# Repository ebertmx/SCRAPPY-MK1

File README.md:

# SCRAPPY-MK1
 A 3D printed robot arm. View documents in project_files for a complete description.
 
 This arm was developed over a 4 week period as an engineering demonstration. Inspired by a previous project, HUEBERT MK2, SCRAPPY consist mostly of 3D printed components and is controllable over the internet (IoT).

The goals of project SCRAPPY were too design and build a robot arm which

1. is highly modular
2. inexpensive
3. had at least 3 DoF
4. could be controlled wireless over a websocket or similar
5. was position and speed controllable
6. used a variety of electrical components (for demonstration purposes)

Other requirements of the specific design can be found in project_files.

The code contained in this respository is designed to run on a 30pin ESP32 Dev module. A python GUI interface is also contained.

This project is ongoing. More details on the use and implementation of this code will be posted when available.

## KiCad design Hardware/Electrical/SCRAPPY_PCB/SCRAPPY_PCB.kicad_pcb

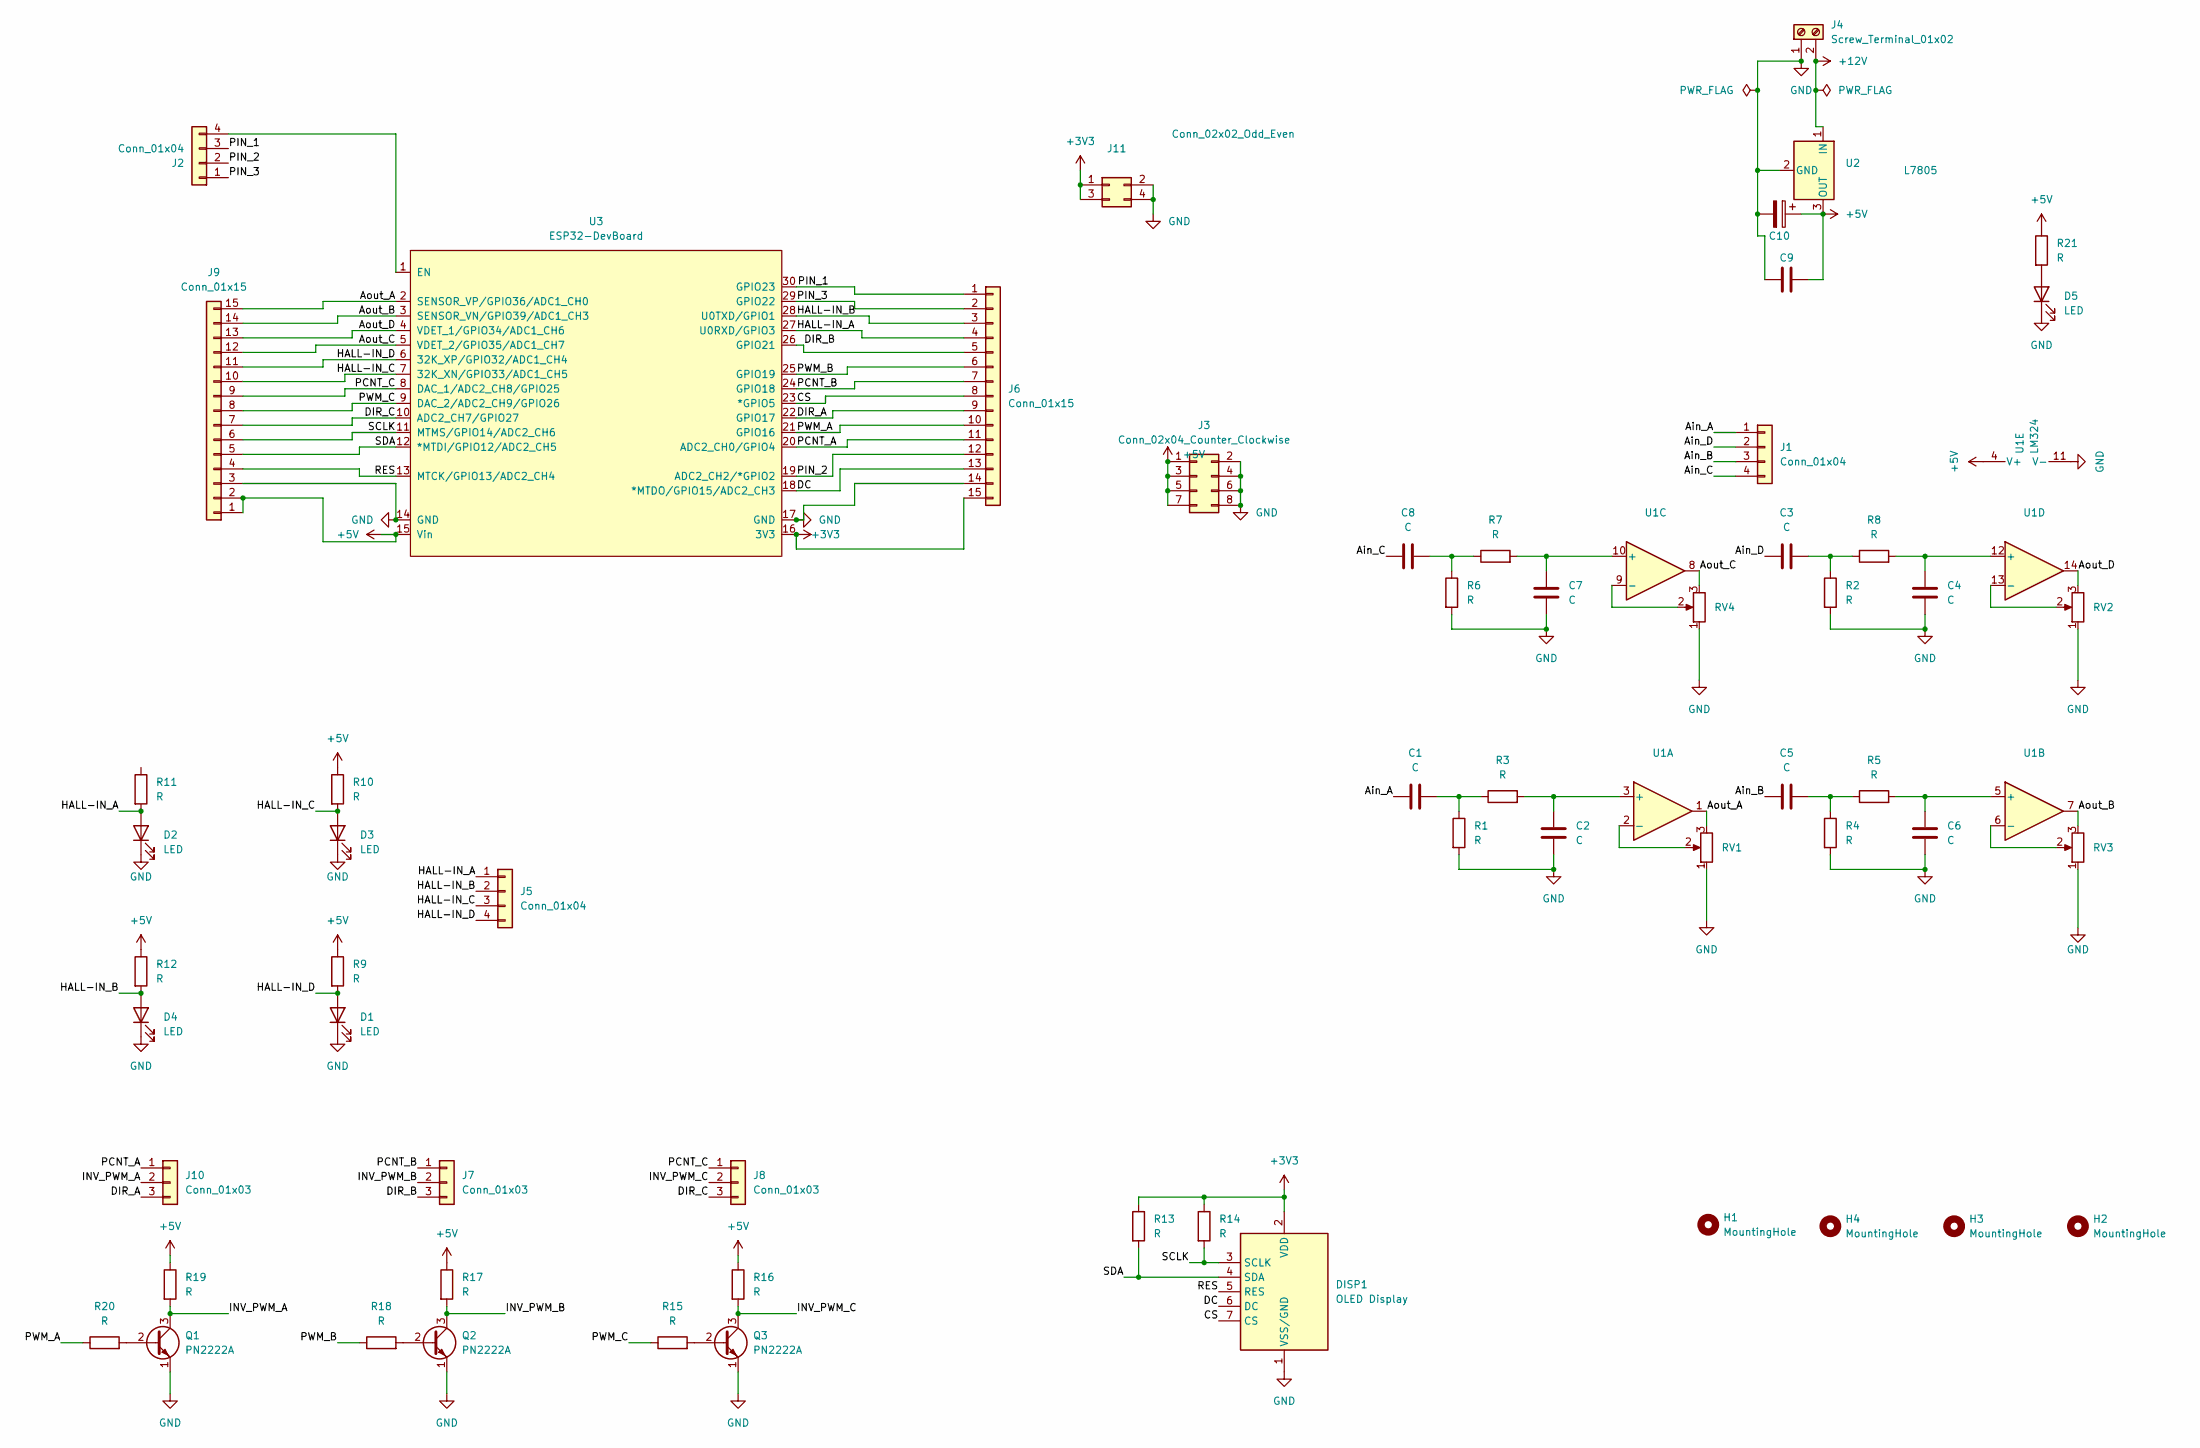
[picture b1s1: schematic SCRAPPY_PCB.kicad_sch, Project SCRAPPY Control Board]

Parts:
C1, C2, C3, C4, C5, C6, C7, C8, C9: C; C_Disc_D3.0mm_W1.6mm_P2.50mm
C10: C_Polarized; CP_Radial_D6.3mm_P2.50mm
D1, D2, D3, D4, D5: LED; LED_D5.0mm_Clear
DISP1: OLED Display; PinHeader_1x07_P2.54mm_Horizontal
H1, H2, H3, H4: MountingHole; MountingHole_2.2mm_M2_DIN965_Pad
J1, J2, J5: Conn_01x04; PinHeader_1x04_P2.54mm_Vertical
J3: Conn_02x04_Counter_Clockwise; PinHeader_2x04_P2.54mm_Vertical
J4: Screw_Terminal_01x02; TerminalBlock_Phoenix_MKDS-1,5-2-5.08_1x02_P5.08mm_Horizont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
J6, J9: Conn_01x15; PinSocket_1x15_P2.54mm_Vertical
J7, J8, J10: Conn_01x03; PinHeader_1x03_P2.54mm_Vertical
J11: Conn_02x02_Odd_Even; PinHeader_1x04_P2.54mm_Vertical
Q1, Q2, Q3: PN2222A; TO-92_Inline_Wide
R1, R2, R3, R4, R5, R6, R7, R8, R9, R10, R11, R12, R13, R14, R15, R16, R17, R18, R19, R20, R21: R; R_Axial_DIN0207_L6.3mm_D2.5mm_P10.16mm_Horizontal
RV1, RV2, RV3, RV4: R_Potentiometer; Potentiometer_Bourns_3296W_Vertical
U1: LM324; DIP-14_W7.62mm_Socket_LongPads
U2: L7805; Converter_DCDC_RECOM_R-78B-2.0_THT
U3: ESP32-DevBoard

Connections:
+3V3: DISP1.2 (VDD), J6.15, J11.1, J11.3, R13.1, R14.1, U3.16 (3V3)
+5V: C9.2, C10.1, J3.1, J3.3, J3.5, J3.7, J9.1, J9.2, R9.1, R10.1, R12.1, R16.1, R17.1, R19.1, R21.1, U1.4 (V+), U2.3 (OUT), U3.15 (Vin)
+12V: J4.2, U2.1 (IN)
/Ain_A: C1.1, J1.1
/Ain_B: C5.1, J1.3
/Ain_C: C8.1, J1.4
/Ain_D: C3.1, J1.2
/Aout_A: J9.15, RV1.3, U1.1, U3.2 (SENSOR_VP/GPIO36/ADC1_CH0)
/Aout_B: J9.14, RV3.3, U1.7, U3.3 (SENSOR_VN/GPIO39/ADC1_CH3)
/Aout_C: J9.12, RV4.3, U1.8, U3.5 (VDET_2/GPIO35/ADC1_CH7)
/Aout_D: J9.13, RV2.3, U1.14, U3.4 (VDET_1/GPIO34/ADC1_CH6)
/CS: DISP1.7 (CS), J6.8, U3.23 (*GPIO5)
/DC: DISP1.6 (DC), J6.13, U3.18 (*MTDO/GPIO15/ADC2_CH3)
/DIR_A: J6.9, J10.3, U3.22 (GPIO17)
/DIR_B: J6.5, J7.3, U3.26 (GPIO21)
/DIR_C: J8.3, J9.7, U3.10 (ADC2_CH7/GPIO27)
/HALL-IN_A: D2.2 (A), J5.1, J6.4, R11.2, U3.27 (U0RXD/GPIO3)
/HALL-IN_B: D4.2 (A), J5.2, J6.3, R12.2, U3.28 (U0TXD/GPIO1)
/HALL-IN_C: D3.2 (A), J5.3, J9.10, R10.2, U3.7 (32K_XN/GPIO33/ADC1_CH5)
/HALL-IN_D: D1.2 (A), J5.4, J9.11, R9.2, U3.6 (32K_XP/GPIO32/ADC1_CH4)
/INV_PWM_A: J10.2, Q1.3 (C), R19.2
/INV_PWM_B: J7.2, Q2.3 (C), R17.2
/INV_PWM_C: J8.2, Q3.3 (C), R16.2
/PCNT_A: J6.11, J10.1, U3.20 (ADC2_CH0/GPIO4)
/PCNT_B: J6.7, J7.1, U3.24 (GPIO18)
/PCNT_C: J8.1, J9.9, U3.8 (DAC_1/ADC2_CH8/GPIO25)
/PIN_1: J2.3, J6.1, U3.30 (GPIO23)
/PIN_2: J2.2, J6.12, U3.19 (ADC2_CH2/*GPIO2)
/PIN_3: J2.1, J6.2, U3.29 (GPIO22)
/PWM_A: J6.10, R20.1, U3.21 (GPIO16)
/PWM_B: J6.6, R18.1, U3.25 (GPIO19)
/PWM_C: J9.8, R15.1, U3.9 (DAC_2/ADC2_CH9/GPIO26)
/RES: DISP1.5 (RES), J9.4, U3.13 (MTCK/GPIO13/ADC2_CH4)
/SCLK: DISP1.3 (SCLK), J9.6, R14.2, U3.11 (MTMS/GPIO14/ADC2_CH6)
/SDA: DISP1.4 (SDA), J9.5, R13.2, U3.12 (*MTDI/GPIO12/ADC2_CH5)
GND: C2.1, C4.1, C6.1, C7.1, C9.1, C10.2, D1.1 (K), D2.1 (K), D3.1 (K), D4.1 (K), D5.1 (K), DISP1.1 (VSS/GND), J3.2, J3.4, J3.6, J3.8, J4.1, J6.14, J9.3, J11.2, J11.4, Q1.1 (E), Q2.1 (E), Q3.1 (E), R1.2, R2.2, R4.2, R6.2, RV1.1, RV2.1, RV3.1, RV4.1, U1.11 (V-), U2.2 (GND), U3.14 (GND), U3.17 (GND)
unnamed: C1.2, R1.1, R3.1
unnamed: C2.2, R3.2, U1.3 (+)
unnamed: C3.2, R2.1, R8.1
unnamed: C4.2, R8.2, U1.12 (+)
unnamed: C5.2, R4.1, R5.1
unnamed: C6.2, R5.2, U1.5 (+)
unnamed: C7.2, R7.2, U1.10 (+)
unnamed: C8.2, R6.1, R7.1
unnamed: D5.2 (A), R21.2
unnamed: J2.4, U3.1 (EN)
unnamed: Q1.2 (B), R20.2
unnamed: Q2.2 (B), R18.2
unnamed: Q3.2 (B), R15.2
unnamed: RV1.2, U1.2 (-)
unnamed: RV2.2, U1.13 (-)
unnamed: RV3.2, U1.6 (-)
unnamed: RV4.2, U1.9 (-)

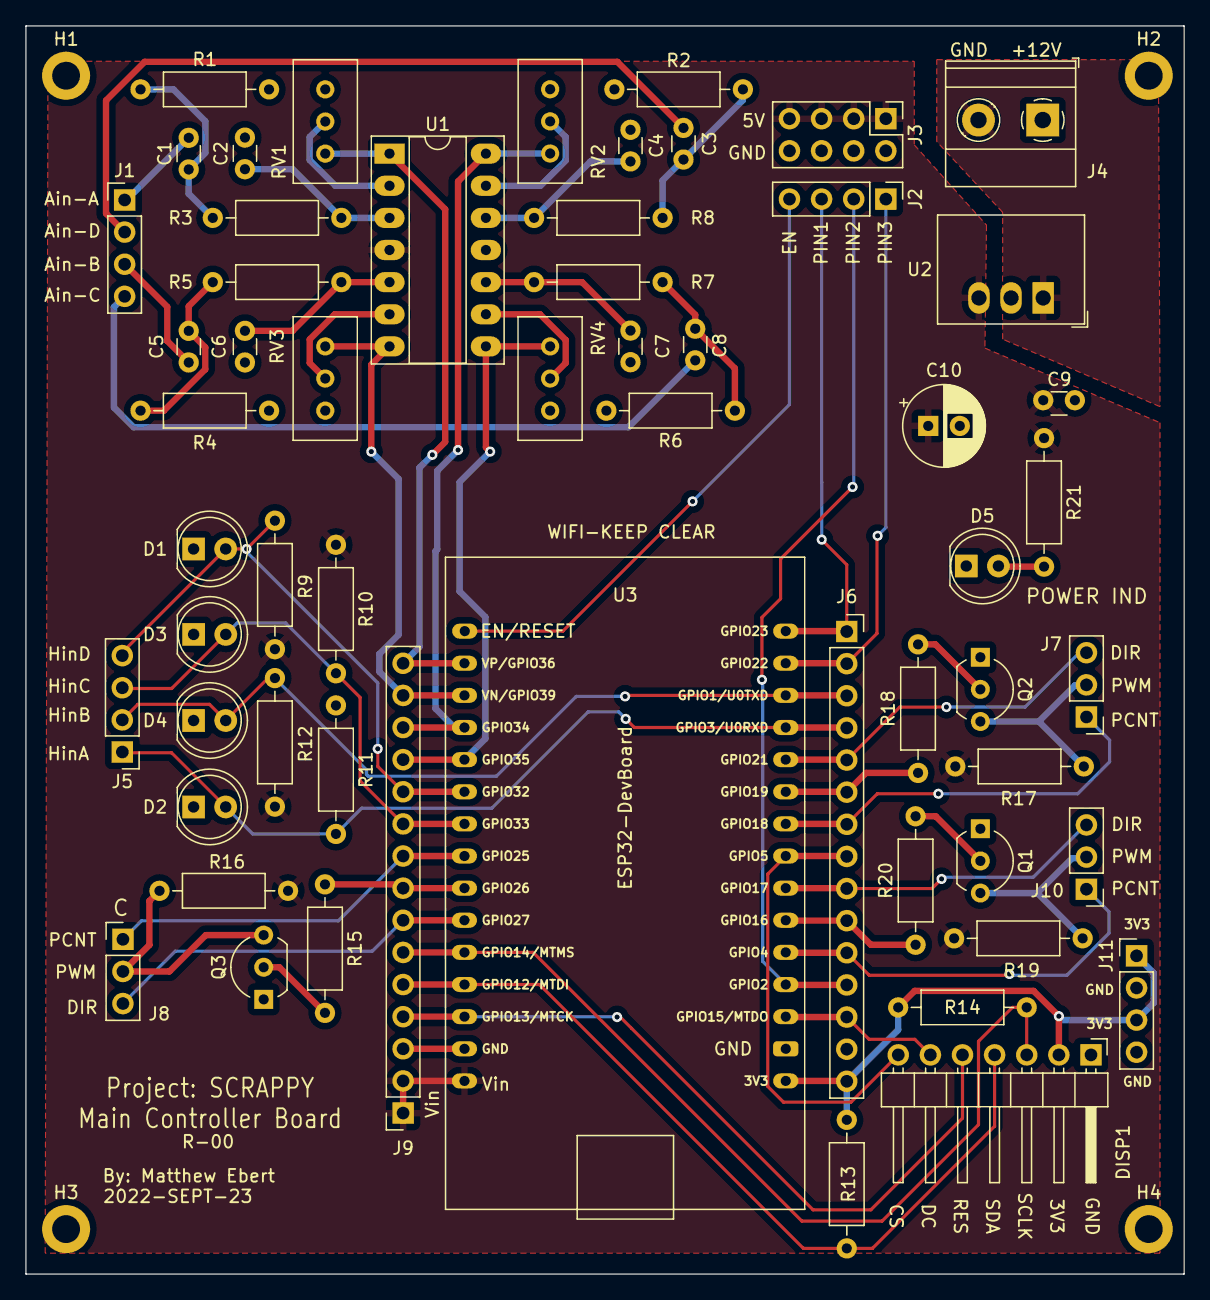
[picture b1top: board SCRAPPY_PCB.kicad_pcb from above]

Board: 2 copper layers, 91.6 x 98.7 mm, 62 parts (0 on the bottom side), 53 nets.

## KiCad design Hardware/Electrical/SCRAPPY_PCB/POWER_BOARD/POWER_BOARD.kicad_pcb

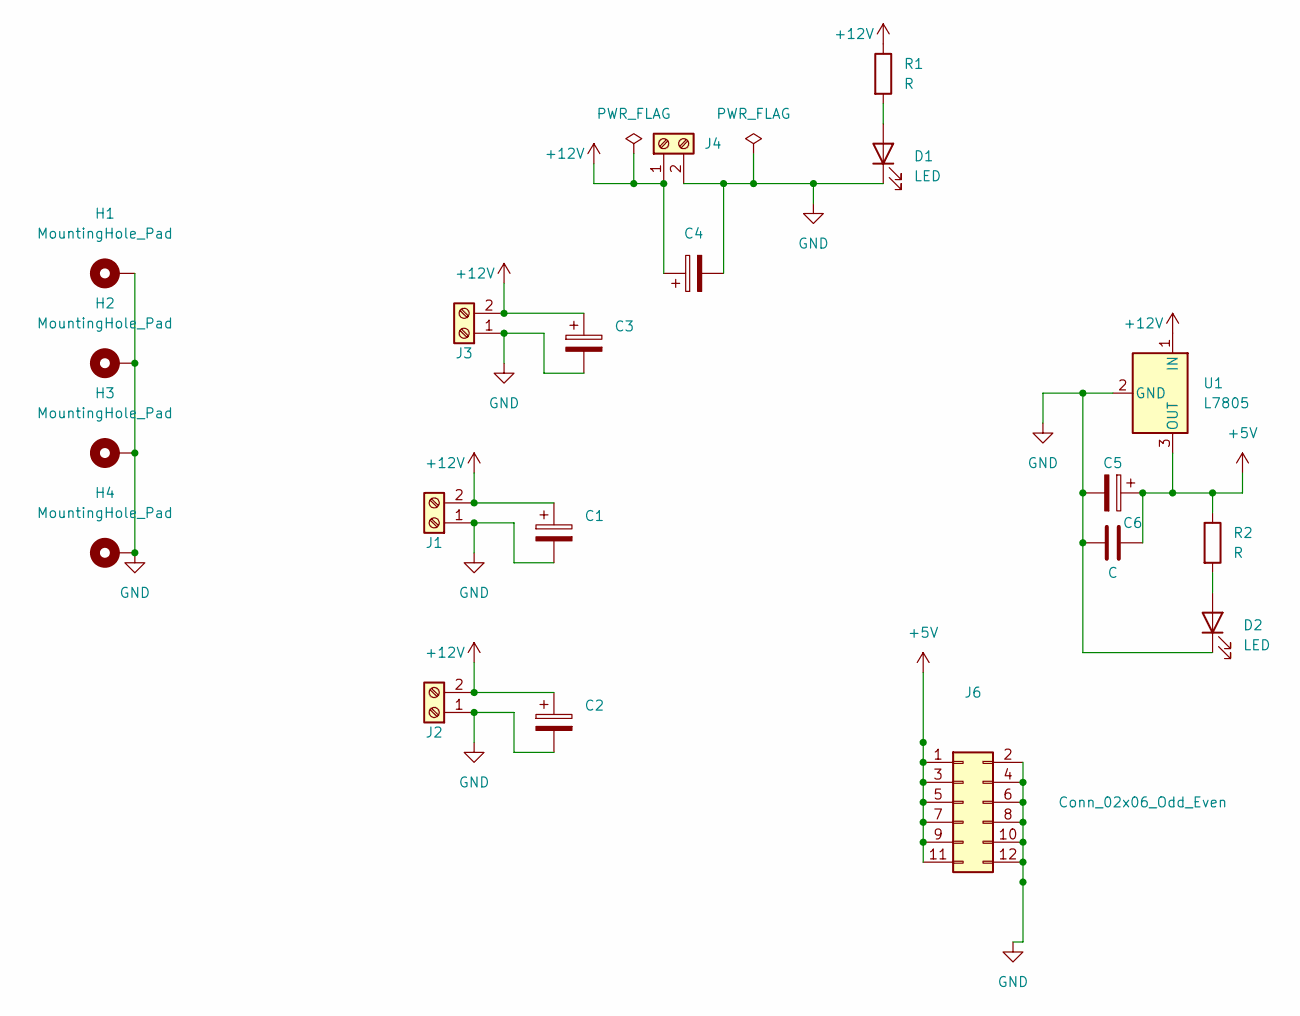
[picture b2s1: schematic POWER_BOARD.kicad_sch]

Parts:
C1, C2, C3, C5: C_Polarized; CP_Radial_D6.3mm_P2.50mm
C4: C_Polarized; CP_Radial_D10.0mm_P5.00mm
C6: C; C_Disc_D5.0mm_W2.5mm_P2.50mm
D1, D2: LED; LED_D5.0mm
H1, H2, H3, H4: MountingHole_Pad; MountingHole_2.2mm_M2_DIN965_Pad
J1, J2, J3, J4: Screw_Terminal_01x02; TerminalBlock_Phoenix_MKDS-1,5-2_1x02_P5.00mm_Horizontal
J6: Conn_02x06_Odd_Even; PinHeader_2x06_P2.54mm_Vertical
R1, R2: R; R_Axial_DIN0207_L6.3mm_D2.5mm_P10.16mm_Horizontal
U1: L7805; Converter_DCDC_Murata_OKI-78SR_Vertical

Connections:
+5V: C5.1, C6.2, J6.1, J6.3, J6.5, J6.7, J6.9, J6.11, R2.1, U1.3 (OUT)
+12V: C1.1, C2.1, C3.1, C4.1, J1.2, J2.2, J3.2, J4.1, R1.1, U1.1 (IN)
GND: C1.2, C2.2, C3.2, C4.2, C5.2, C6.1, D1.1 (K), D2.1 (K), H1.1, H2.1, H3.1, H4.1, J1.1, J2.1, J3.1, J4.2, J6.2, J6.4, J6.6, J6.8, J6.10, J6.12, U1.2 (GND)
unnamed: D1.2 (A), R1.2
unnamed: D2.2 (A), R2.2

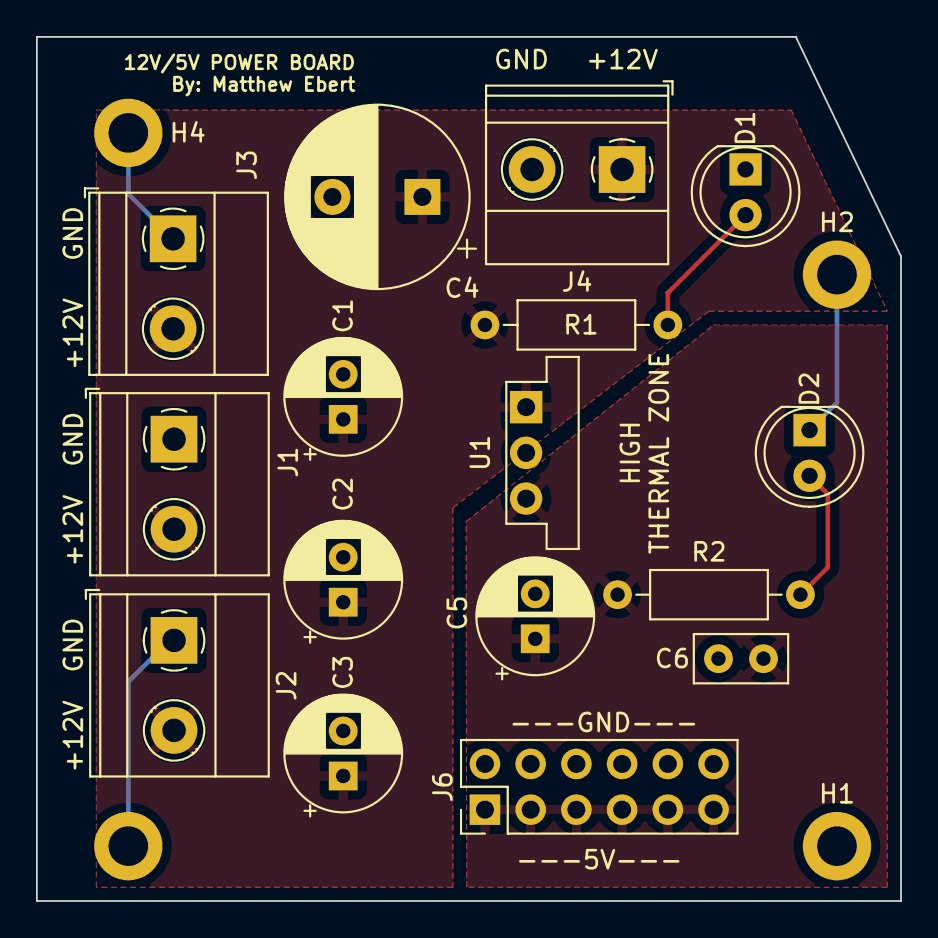
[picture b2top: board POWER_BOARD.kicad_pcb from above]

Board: 2 copper layers, 48.0 x 48.0 mm, 20 parts (1 on the bottom side), 5 nets.

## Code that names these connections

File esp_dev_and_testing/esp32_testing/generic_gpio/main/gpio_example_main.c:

/* GPIO Example

   This example code is in the Public Domain (or CC0 licensed, at your option.)

   Unless required by applicable law or agreed to in writing, this
   software is distributed on an "AS IS" BASIS, WITHOUT WARRANTIES OR
   CONDITIONS OF ANY KIND, either express or implied.
*/
#include <stdio.h>
#include <string.h>
#include <stdlib.h>
#include "freertos/FreeRTOS.h"
#include "freertos/task.h"
#include "freertos/queue.h"
#include "driver/gpio.h"
/**
 * Brief:
 * This test code shows how to configure gpio and how to use gpio interrupt.
 *
 * GPIO status:
 * GPIO18: output
 * GPIO19: output
 * GPIO4:  input, pulled up, interrupt from rising edge and falling edge
 * GPIO5:  input, pulled up, interrupt from rising edge.
 *
 * Test:
 * Connect GPIO18 with GPIO4
 * Connect GPIO19 with GPIO5
 * Generate pulses on GPIO18/19, that triggers interrupt on GPIO4/5
 *
 */

#define GPIO_OUTPUT_IO_0    18
#define GPIO_OUTPUT_IO_1    19
#define GPIO_OUTPUT_PIN_SEL  ((1ULL<<GPIO_OUTPUT_IO_0) | (1ULL<<GPIO_OUTPUT_IO_1))
#define GPIO_INPUT_IO_0     4
#define GPIO_INPUT_IO_1     5
#define GPIO_INPUT_PIN_SEL  ((1ULL<<GPIO_INPUT_IO_0) | (1ULL<<GPIO_INPUT_IO_1))
#define ESP_INTR_FLAG_DEFAULT 0

static xQueueHandle gpio_evt_queue = NULL;

static void IRAM_ATTR gpio_isr_handler(void* arg)
{
    uint32_t gpio_num = (uint32_t) arg;
    xQueueSendFromISR(gpio_evt_queue, &gpio_num, NULL);
}

static void gpio_task_example(void* arg)
{
    uint32_t io_num;
    for(;;) {
        if(xQueueReceive(gpio_evt_queue, &io_num, portMAX_DELAY)) {
            printf("GPIO[%d] intr, val: %d\n", io_num, gpio_get_level(io_num));
        }
    }
}

void app_main(void)
{
    // //zero-initialize the config structure.
    // gpio_config_t io_conf = {};
    // //disable interrupt
    // io_conf.intr_type = GPIO_INTR_DISABLE;
    // //set as output mode
    // io_conf.mode = GPIO_MODE_OUTPUT;
    // //bit mask of the pins that you want to set,e.g.GPIO18/19
    // io_conf.pin_bit_mask = GPIO_OUTPUT_PIN_SEL;
    // //disable pull-down mode
    // io_conf.pull_down_en = 0;
    // //disable pull-up mode
    // io_conf.pull_up_en = 0;
    // //configure GPIO with the given settings
    // gpio_config(&io_conf);

    // //interrupt of rising edge
    // io_conf.intr_type = GPIO_INTR_POSEDGE;
    // //bit mask of the pins, use GPIO4/5 here
    // io_conf.pin_bit_mask = GPIO_INPUT_PIN_SEL;
    // //set as input mode
    // io_conf.mode = GPIO_MODE_INPUT;
    // //enable pull-up mode
    // io_conf.pull_up_en = 1;
    // gpio_config(&io_conf);

    // //change gpio intrrupt type for one pin
    // gpio_set_intr_type(GPIO_INPUT_IO_0, GPIO_INTR_ANYEDGE);

    // //create a queue to handle gpio event from isr
    // gpio_evt_queue = xQueueCreate(10, sizeof(uint32_t));
    // //start gpio task
    // xTaskCreate(gpio_task_example, "gpio_task_example", 2048, NULL, 10, NULL);

    // //install gpio isr service
    // gpio_install_isr_service(ESP_INTR_FLAG_DEFAULT);
    // //hook isr handler for specific gpio pin
    // gpio_isr_handler_add(GPIO_INPUT_IO_0, gpio_isr_handler, (void*) GPIO_INPUT_IO_0);
    // //hook isr handler for specific gpio pin
    // gpio_isr_handler_add(GPIO_INPUT_IO_1, gpio_isr_handler, (void*) GPIO_INPUT_IO_1);

    // //remove isr handler for gpio number.
    // gpio_isr_handler_remove(GPIO_INPUT_IO_0);
    // //hook isr handler for specific gpio pin again
    // gpio_isr_handler_add(GPIO_INPUT_IO_0, gpio_isr_handler, (void*) GPIO_INPUT_IO_0);

    // printf("Minimum free heap size: %d bytes\n", esp_get_minimum_free_heap_size());
    gpio_set_direction(GPIO_NUM_22, GPIO_MODE_OUTPUT);
     int cnt = 0;
    while(1) {
        printf("cnt: %d\n", cnt++);
        vTaskDelay(1000 / portTICK_RATE_MS);
        gpio_set_level(GPIO_NUM_22, cnt%2);
        printf("gpio level of %d:  ", GPIO_NUM_2);
        //gpio_set_level(GPIO_OUTPUT_IO_1, cnt % 2);
    }


}

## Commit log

2022-09-21 Initial Project Files
2022-09-21 Update Req
2022-09-21 Added testing and development files for the ESP devices
2022-09-23 Created initial PCB design
2022-09-23 Updated PCB; Ready for Manufacture
2022-09-24 Added Power PCB
2022-09-24 PCB Ordered
2022-09-27 Update design documents
2022-09-27 Updated Docs
2022-10-01 Added start of state chart
2022-10-02 Updated Build
2022-10-02 Updated REQS
2022-10-04 Added Movement_Control dev project
2022-10-04 Added Position Controller and created ARCHIVE files
2022-10-07 Git Ignore Still not working
2022-10-08 Adding control server/serialreader/gui
    Note serial_reader is not tested
2022-10-08 WIP esp32_controller
    work in progress on the esp32 control software
2022-10-09 Updated SCRAPPY CONTROLLER
    Working Simple Motor
2022-10-09 Updated for scrappy pins
2022-10-10 Fixed PCNT counter bugs
2022-10-10 Added Wifi Connect
2022-10-10 Updated for testing
2022-10-10 Added Calibration code
2022-10-10 Updated Calibration
2022-10-11 Updated Controller with Calibration step
2022-10-11 Connor's changes
2022-10-11 Got WIFI control working
2022-10-11 Updated move to work on SCRAPPY disabled LOGGING
2022-10-11 fixed bugs
2022-10-11 UPdated Calibrate
2022-10-11 Update Calibration
2022-10-11 Update Speed
2022-10-11 Prepared For Demo
2022-10-11 Added presentation
2022-10-11 PANIC
2022-10-14 Added new controller module
2022-10-14 Updating gui code
2022-10-15 Update MovementController for 3 motors
2022-10-15 updated controller
2022-10-15 Buttons and WIP refactor
2022-10-15 Bug fixes with control signal
2022-10-16 Control Demo is active and working. Network is down and commented
2022-10-17 Bugfixes for main.c
2022-10-17 Added serial reading
2022-10-17 Added calibration
2022-10-17 Added calibration button
2022-10-17 Updated main for use Still bugs but in decent condition
2022-10-17 serial quality of life
2022-10-17 Good state; About to test SKIPPY integration
2022-10-17 adding scrollbar
2022-10-17 Fixed serial startup issue
2022-10-17 M's to P's
2022-10-17 Take the night off
2022-10-17 Link 1 SKIPPY operational
2022-10-17 Successful Test with SKIPPY integration
2022-10-17 Added Skippy Code; Deleted Old Calibration
2022-10-17 Visual update
2022-10-18 Magnet code
2022-10-18 vgu bugfix
2022-10-19 Working Night of
2022-10-20 Magnet button
2022-10-21 Added auto move test button
2022-10-21 Working Test demo
2023-01-10 Revert "updated readme"
    This reverts commit 0c46d2d876b9ec99ae3838effcb00f295e4baa2d.
2023-03-05 Updated structure
